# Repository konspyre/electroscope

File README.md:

# Toy Electroscope

Elsewhere: Check out the [through-hole version](https://github.com/konspyre/electroscope-through) of this electroscope

This is an Electroscope done up using a design from Alan "vk2zay" Yates in his [Making Electrets](http://www.youtube.com/watch?v=1DR-tTU8uIM) video.

### Postings

[Updated electroscope](http://open.konspyre.org/blog/2015-02-10-electroscope-update/)

[Initial release](http://open.konspyre.org/blog/2014/05/30/electroscope/)

### Direct fabrication

Latest/updated (use this one): [Updated electroscope (OSHPark shared project)](https://oshpark.com/shared_projects/x89XVFQf)

Older: [Old electroscope (OSHPark shared project)](https://www.oshpark.com/shared_projects/KFA2jmSs)

### Bill of Materials

This BOM specifies the amount needed for _one_ board.

| Quantity | Description | Digikey Part Number | Board Placement |
| -------- | ----------- | ----------- | --------------- |
| 3        | 2N3906      | [MMBT3906FSCT-ND](http://www.digikey.com/product-detail/en/MMBT3906/MMBT3906FSCT-ND/458972) | Right (label: 2N3906) |
| 3 	   | 2N3904	 | [MMBT3904FSCT-ND](http://www.digikey.com/product-detail/en/MMBT3904/MMBT3904FSCT-ND/458971) | Left (label: 2N3904) |
| 2        | 100 ohm resistor (0603 imperial) | [1276-5038-1-ND](http://www.digikey.com/product-detail/en/RC1608J101CS/1276-5038-1-ND/) | Bottom (label: 100 ohm) |
| 2        | 100k ohm resistor (0603 imperial) | [1276-5110-1-ND](http://www.digikey.com/product-detail/en/RC1608J104CS/1276-5110-1-ND) | Middle (label: 100k ohm) |
| 2	   | 1M ohm resistor (0603 imperial) | [311-1.00MHRCT-ND](http://www.digikey.com/product-detail/en/RC0603FR-071ML/311-1.00MHRCT-ND/) | Top (label: 1M ohm) |
| 1        | 9v female PCB mount snap | [BSPCF](http://www.digikey.com/product-search/en?vendor=0&keywords=BSPCF) | 9V+ terminal (verify before soldering by attaching to a 9V battery -- reworking afterwards is difficult without specialized tools/materials) |
| 1        | 9v male PCB mount snap | [BSPCM](http://www.digikey.com/product-search/en?vendor=0&keywords=BSPCM) |  9V- terminal (verify before soldering by attaching to a 9V battery -- reworking afterwards is difficult without specialized tools/materials) |

#### LEDs

_Pick either the 3mm LEDs or surface mount 0805s_

| Quantity | Description | Digikey Part Number | Board Placement |
| -------- | ----------- | ----------- | --------------- |
| 2        | 3mm LEDs | (Red: [160-1704-ND](http://www.digikey.com/product-search/en?vendor=0&keywords=160-1704-ND) / Green: [160-1958-ND](http://www.digikey.com/product-search/en?vendor=0&keywords=160-1958-ND) | Bottom (verify orientation before soldering!) |
| 2        | 0805 imperial LEDs | (Orange: [350-2040-1-ND](http://www.digikey.com/product-search/en?vendor=0&keywords=350-2040-1-ND) / Yellow: [350-2041-1-ND](http://www.digikey.com/product-search/en?vendor=0&keywords=350-2041-1-ND) | Bottom (verify orientation as with the 3mm LEDs) |

#### Antenna

There is no part for this, so you'll have to make your own. A simple loop soldered together usually
works well (the twisted termination used in the [previous photos](https://open.konspyre.org/assets/images/electroscope/top-old-ver-kapton.png) is just a fancy flourish).

#### Optional

Shielding: I experimented with a three-layered combination of kapton/polymide tape (to cover the BJTs), copper tape (edge to edge, touching the exposed ground edges), and then another layer of kapton/polymide to keep the copper looking nicely unscuffed by oils (from fingers).

### License

[CC0 1.0 Universal](https://creativecommons.org/publicdomain/zero/1.0)

Original design/schematic by [Alan "vk2zay" Yates](http://twitter.com/vk2zay)

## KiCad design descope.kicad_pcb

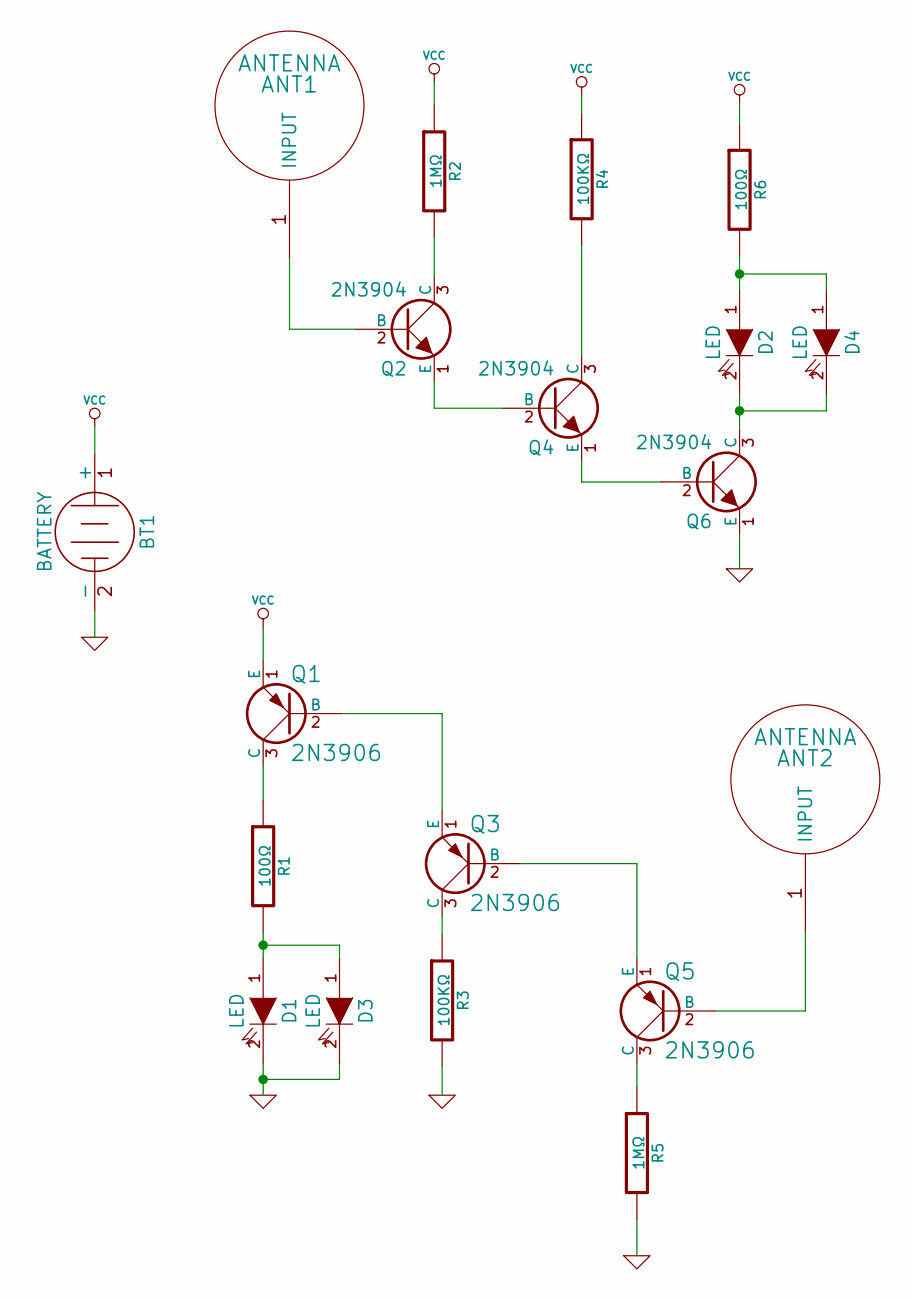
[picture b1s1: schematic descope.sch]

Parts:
ANT1, ANT2: ANTENNA
BT1: BATTERY
D1, D2, D3, D4: LED
Q1, Q3, Q5: 2N3906
Q2, Q4, Q6: 2N3904
R1, R6: 100Ω
R2, R5: 1MΩ
R3, R4: 100KΩ

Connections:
GND: BT1.2 (-), D1.2 (K), D3.2 (K), Q6.1 (E), R3.2, R5.2
unnamed: ANT1.1, Q2.2 (B)
unnamed: Q1.2 (B), Q3.1 (E)
unnamed: Q4.3 (C), R4.2
unnamed: Q4.1 (E), Q6.2 (B)
unnamed: Q2.1 (E), Q4.2 (B)
unnamed: Q2.3 (C), R2.2
unnamed: D1.1 (A), D3.1 (A), R1.2
unnamed: D2.2 (K), D4.2 (K), Q6.3 (C)
unnamed: D2.1 (A), D4.1 (A), R6.2
unnamed: ANT2.1, Q5.2 (B)
unnamed: Q5.3 (C), R5.1
unnamed: Q3.3 (C), R3.1
unnamed: Q1.3 (C), R1.1
unnamed: Q3.2 (B), Q5.1 (E)
VCC: BT1.1 (+), Q1.1 (E), R2.1, R4.1, R6.1

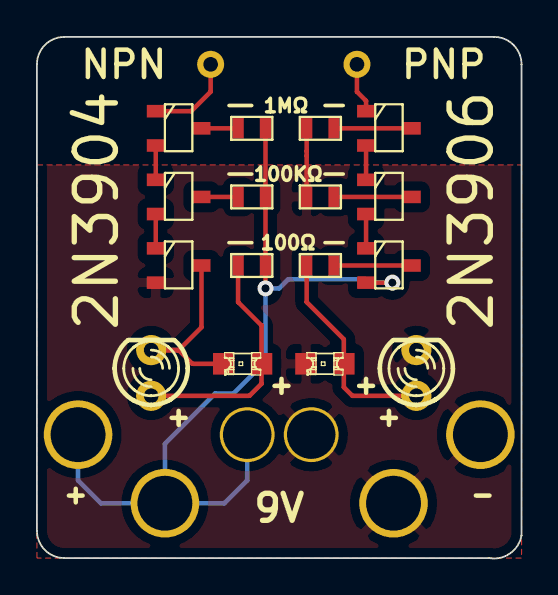
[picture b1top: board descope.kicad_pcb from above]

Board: 2 copper layers, 26.9 x 29.0 mm, 19 parts (0 on the bottom side), 16 nets.

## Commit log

2014-05-30 Initial commit
    This is based off of commit 10acfe2 in the previous repository.
2014-05-30 Add README with BOM
2014-05-30 Fix image
2014-05-30 Use a somewhat better looking picture
2014-05-30 Add Digikey links!
2014-05-30 Add blog post link
2014-05-30 Add a license
2014-05-30 Clean up README
2014-05-30 Direct part links
2014-05-30 Credits
2014-06-04 Add notes to 9v male part
2014-08-19 Update electroscope for fabrication
    Vendor: OSHPark, LLC
2014-08-29 Eliminate copper pours
2014-09-01 No copper pours version
    Fabricator: OSHPark, LLC
2014-10-09 Restore copper planes, keeping most recent features as well
2014-10-10 Update for fabrication
    * Remove some extraneous traces since we're going back to copper pours.
    Some of the traces are still intact from the non-pour version so that it is
    easy to go back and forth (two traces removed)
    * Added a white silk area on the back for notes (like bad/good/sensitivity/config notes)
    Fabricator: OSHPark, LLC
2014-10-10 Add production gerbers
2015-02-09 Add fabbed/generated gerbers
2015-02-09 Remove backup files
2015-02-09 Updated electroscope with pulled back copper pour
2015-02-13 Update electroscope documentation
2015-02-13 CC0 1.0 Universal
2018-10-07 README: Add a link to the previous electroscope
2019-04-14 README: Add a link to the through-hole version
